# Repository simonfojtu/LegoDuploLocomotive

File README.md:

# Lego DUPLO remote controlled locomotive

Modifying Lego DUPLO machine to be remote controlled.

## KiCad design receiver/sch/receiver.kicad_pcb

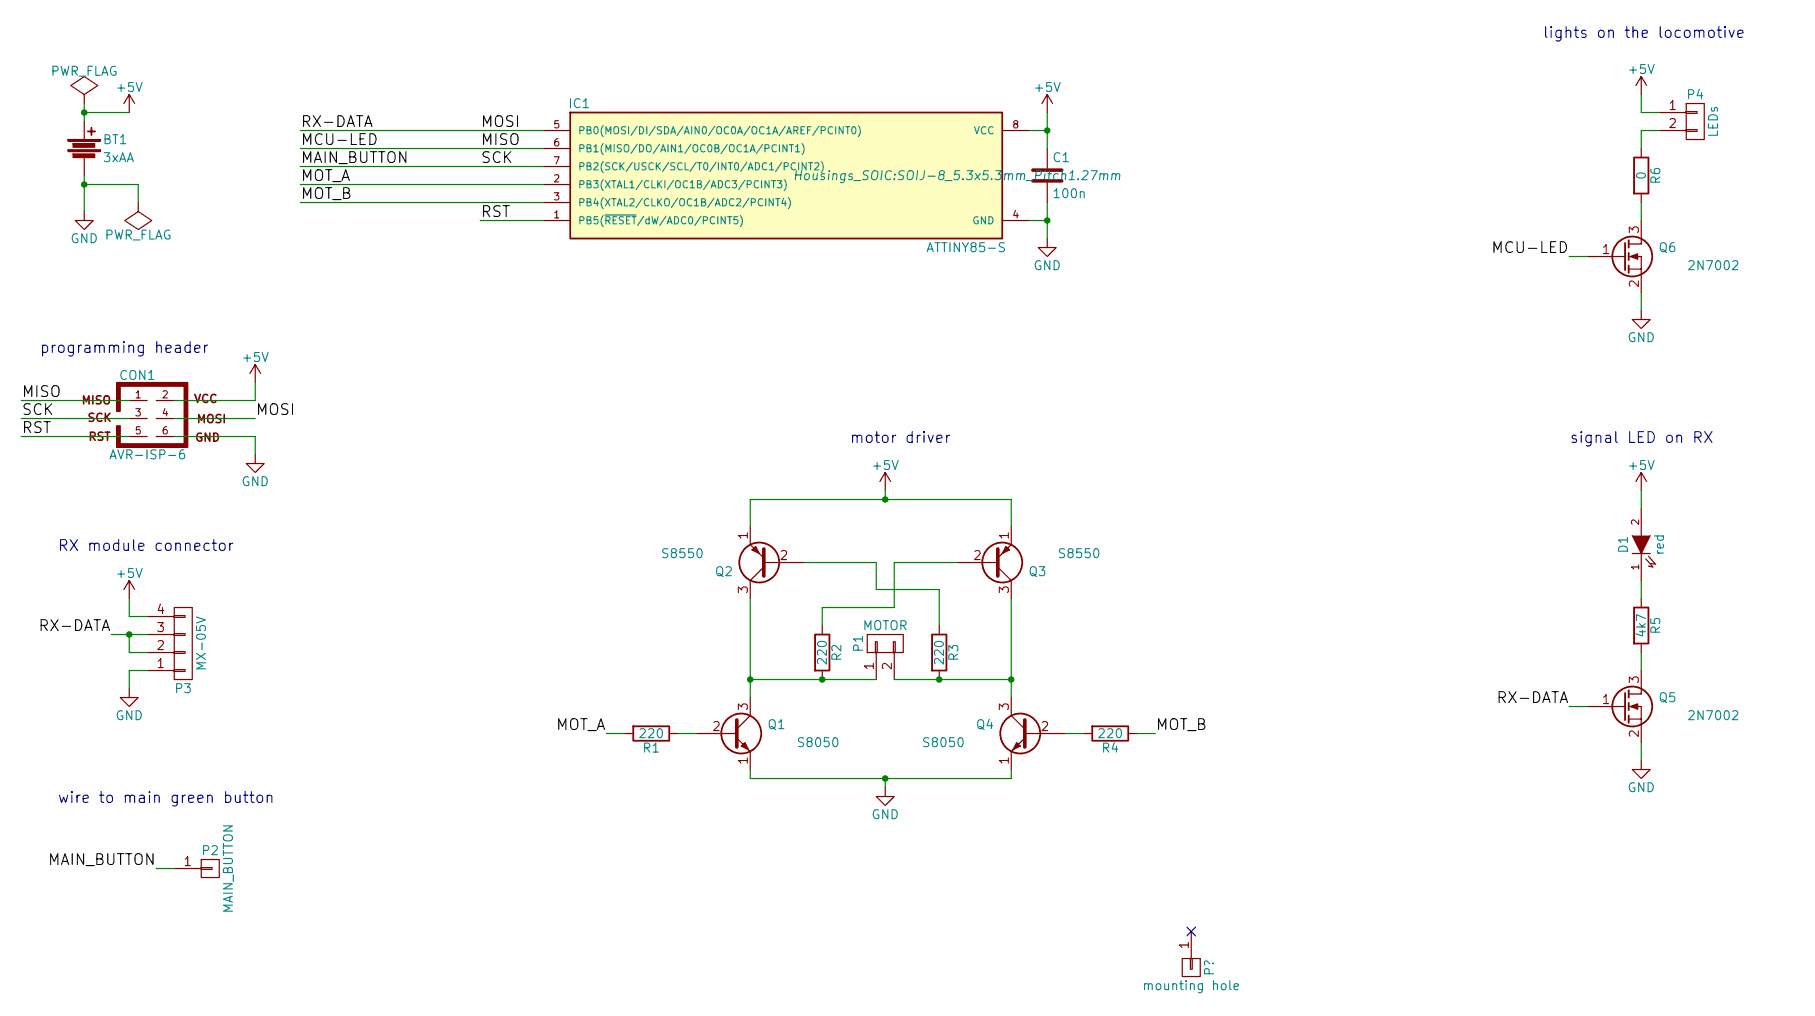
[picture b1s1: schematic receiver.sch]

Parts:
BT1: 3xAA; Pin_Header_Straight_1x02
C1: 100n; C_0805_HandSoldering
CON1: AVR-ISP-6; Pin_Header_Straight_2x03
D1: red; LED_0805
IC1: ATTINY85-S; SOIJ-8_5.3x5.3mm_Pitch1.27mm
P1: MOTOR; Pin_Header_Straight_1x02
P2: MAIN_BUTTON; Pin_Header_Straight_1x01
P3: MX-05V; Pin_Header_Straight_1x04
P4: LEDs; Pin_Header_Straight_1x02
Q1, Q4: S8050; TO-92_Inline_Narrow_Oval
Q2, Q3: S8550; TO-92_Inline_Wide
Q5, Q6: 2N7002; SOT-23_Handsoldering
R1, R2, R3, R4: 220; R_0805_HandSoldering
R5: 4k7; R_0805_HandSoldering
R6: 0; R_0805_HandSoldering

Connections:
+5V: BT1.1, C1.1, CON1.2, D1.2 (A), IC1.8 (VCC), P3.4, P4.1, Q2.1 (E), Q3.1 (E)
/MAIN_BUTTON: CON1.3, IC1.7 (PB2(SCK/USCK/SCL/T0/INT0/ADC1/PCINT2)), P2.1
/MCU-LED: CON1.1, IC1.6 (PB1(MISO/DO/AIN1/OC0B/OC1A/PCINT1)), Q6.1 (G)
/MOSI: CON1.4, IC1.5 (PB0(MOSI/DI/SDA/AIN0/OC0A/OC1A/AREF/PCI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), P3.2, P3.3, Q5.1 (G)
/MOT_A: IC1.2 (PB3(XTAL1/CLKI/OC1B/ADC3/PCINT3)), R1.2
/MOT_B: IC1.3 (PB4(XTAL2/CLKO/OC1B/ADC2/PCINT4)), R4.1
/RST: CON1.5, IC1.1 (PB5(~RESET~/dW/ADC0/PCINT5))
GND: BT1.2, C1.2, CON1.6, IC1.4 (GND), P3.1, Q1.1 (E), Q4.1 (E), Q5.2 (S), Q6.2 (S)
unnamed: D1.1 (K), R5.1
unnamed: P1.1, Q1.3 (C), Q2.3 (C), R2.2
unnamed: P1.2, Q3.3 (C), Q4.3 (C), R3.2
unnamed: P4.2, R6.1
unnamed: Q1.2 (B), R1.1
unnamed: Q2.2 (B), R3.1
unnamed: Q3.2 (B), R2.1
unnamed: Q4.2 (B), R4.2
unnamed: Q5.3 (D), R5.2
unnamed: Q6.3 (D), R6.2

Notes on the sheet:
programming header
RX module connector
wire to main green button
motor driver
signal LED on RX
lights on the locomotive

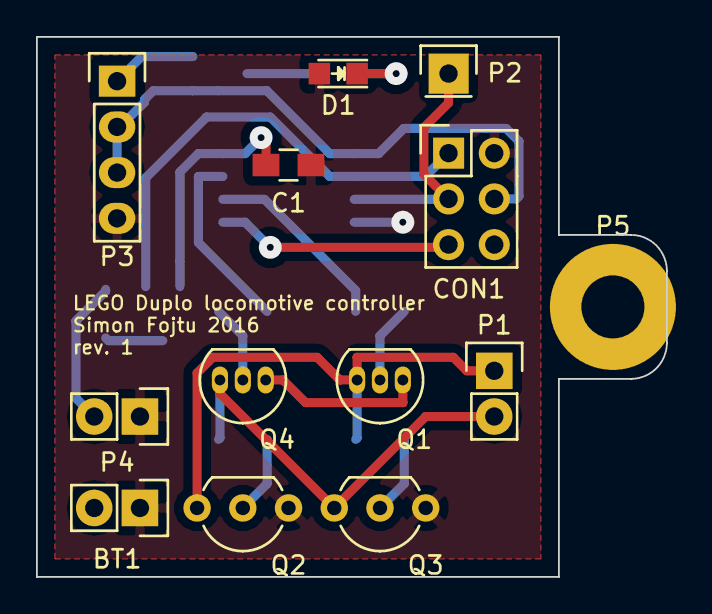
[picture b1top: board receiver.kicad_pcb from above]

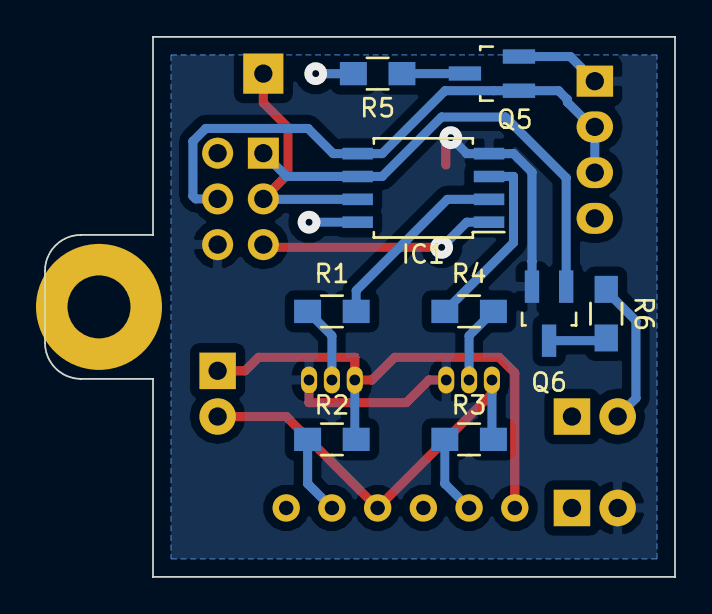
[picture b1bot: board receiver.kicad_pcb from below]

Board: 2 copper layers, 35.0 x 30.0 mm, 22 parts (9 on the bottom side), 18 nets.

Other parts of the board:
P5: mounting hole; MountingHole_3.5mm_Pad

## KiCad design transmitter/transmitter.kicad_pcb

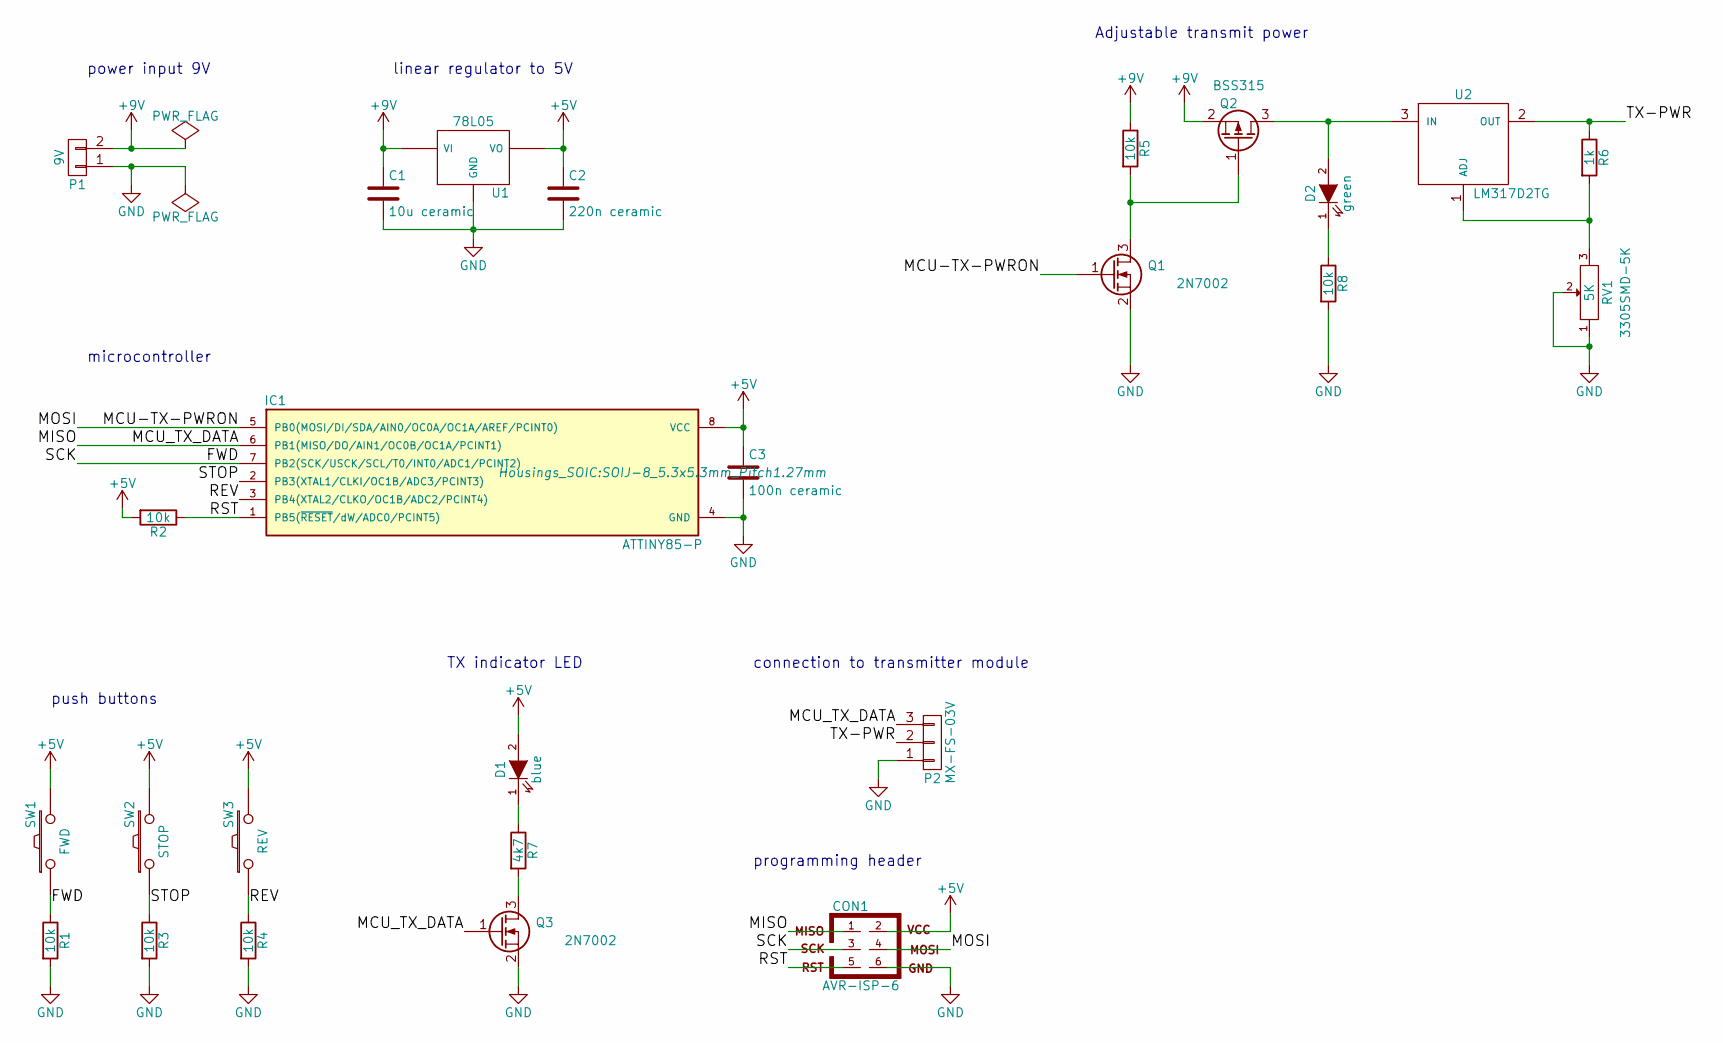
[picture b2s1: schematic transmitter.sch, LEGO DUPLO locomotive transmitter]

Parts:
C1: 10u ceramic; C_0805_HandSoldering
C2: 220n ceramic; C_0805_HandSoldering
C3: 100n ceramic; C_0805_HandSoldering
CON1: AVR-ISP-6; Pin_Header_Straight_2x03
D1: blue; LED-3MM
D2: green; LED-3MM
IC1: ATTINY85-P; SOIJ-8_5.3x5.3mm_Pitch1.27mm
P1: 9V; Pin_Header_Straight_1x02
P2: MX-FS-03V; Pin_Header_Angled_1x03
Q1, Q3: 2N7002; SOT-23_Handsoldering
Q2: BSS315; SOT-23_Handsoldering
R1, R2, R3, R4, R5, R8: 10k; R_0805_HandSoldering
R6: 1k; R_0805_HandSoldering
R7: 4k7; R_0805_HandSoldering
RV1: 5K; POT_SMD
SW1: FWD; SW_PUSH_SMALL
SW2: STOP; SW_PUSH_SMALL
SW3: REV; SW_PUSH_SMALL
U1: 78L05; TO-220_Neutral123_Vertical
U2: LM317D2TG; SOT-404

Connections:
+5V: C2.1, C3.1, CON1.2, D1.2 (A), IC1.8 (VCC), R2.2, SW1.2, SW2.2, SW3.2, U1.3 (VO)
+9V: C1.1, P1.2, Q2.2 (S), R5.1, U1.1 (VI)
/FWD: CON1.3, IC1.7 (PB2(SCK/USCK/SCL/T0/INT0/ADC1/PCINT2)), R1.1, SW1.1
/MCU-TX-PWRON: CON1.4, IC1.5 (PB0(MOSI/DI/SDA/AIN0/OC0A/OC1A/AREF/PCI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), Q1.1 (G)
/MCU_TX_DATA: CON1.1, IC1.6 (PB1(MISO/DO/AIN1/OC0B/OC1A/PCINT1)), P2.3, Q3.1 (G)
/REV: IC1.3 (PB4(XTAL2/CLKO/OC1B/ADC2/PCINT4)), R4.1, SW3.1
/RST: CON1.5, IC1.1 (PB5(~RESET~/dW/ADC0/PCINT5)), R2.1
/STOP: IC1.2 (PB3(XTAL1/CLKI/OC1B/ADC3/PCINT3)), R3.1, SW2.1
/TX-PWR: P2.2, R6.1, U2.2 (OUT)
GND: C1.2, C2.2, C3.2, CON1.6, IC1.4 (GND), P1.1, P2.1, Q1.2 (S), Q3.2 (S), R1.2, R3.2, R4.2, R8.2, RV1.1, RV1.2, U1.2 (GND)
unnamed: D1.1 (K), R7.1
unnamed: D2.1 (K), R8.1
unnamed: D2.2 (A), Q2.3 (D), U2.3 (IN)
unnamed: Q1.3 (D), Q2.1 (G), R5.2
unnamed: Q3.3 (D), R7.2
unnamed: R6.2, RV1.3, U2.1 (ADJ)

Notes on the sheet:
power input 9V
linear regulator to 5V
microcontroller
push buttons
TX indicator LED
connection to transmitter module
programming header
Adjustable transmit power

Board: 2 copper layers, 26 parts (18 on the bottom side), 16 nets, no tracks yet.

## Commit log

2016-07-09 Updated README and log
2016-07-09 Transmitter schematics
2016-07-09 transmitter_1e9f973b79bf1e60976f5d36f49e2bdb1212c23c.pdf
2016-07-09 Revert to pdf
2016-07-09 inline pdf?
2016-07-09 No inline pdf:(
2016-07-10 receiver schematics
2016-07-10 Receiver and transmitter PCB design
2016-07-15 organizing files
2016-07-19 receiver board layout update
2016-07-19 receiver pcb rev.1
2016-07-19 receiver firmware
2016-07-20 button
2016-07-20 some change in receiver pcb
2016-07-20 long/short button press; correct stop/start behaviour
2016-07-20 fixed interrupts and sleep mode; wdt timeout extended to 120s
2016-07-20 receiver-mounting hole
